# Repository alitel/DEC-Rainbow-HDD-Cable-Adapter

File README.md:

# DEC-Rainbow-HDD-Cable-Adapter
This PCB can be used to connect an MFM hard drive (or emulator) to a Dec rainbow 100 using standard ribbon cables.

I followed the cable building guide found here: https://oldcomputers-ddns.org/public/pub/mirror/os2site/sw/dec/rainbow/rainbow.faq

(The instructions are also found in Cable Instructions.txt)

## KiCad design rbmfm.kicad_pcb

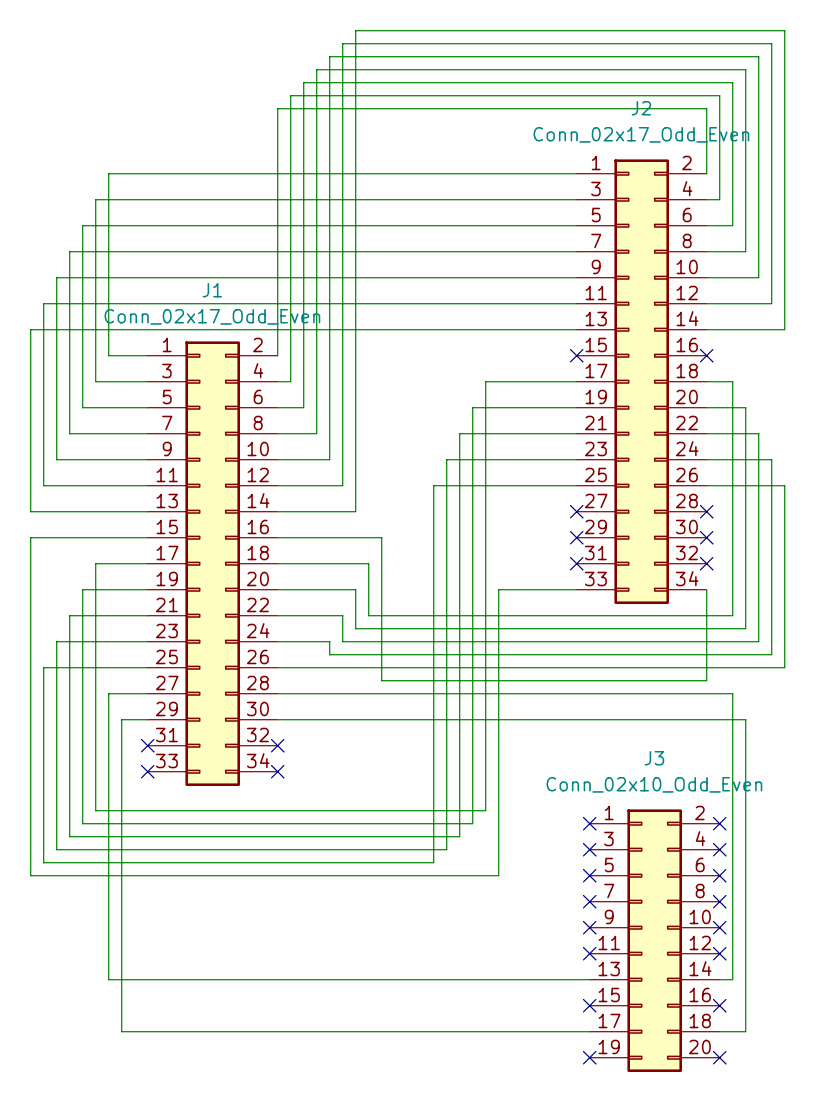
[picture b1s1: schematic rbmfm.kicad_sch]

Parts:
J1, J2: Conn_02x17_Odd_Even; IDC-Header_2x17_P2.54mm_Vertical
J3: Conn_02x10_Odd_Even; IDC-Header_2x10_P2.54mm_Vertical

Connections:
unnamed: J1.1, J2.1
unnamed: J1.2, J2.2
unnamed: J1.3, J2.3
unnamed: J1.4, J2.4
unnamed: J1.5, J2.5
unnamed: J1.6, J2.6
unnamed: J1.7, J2.7
unnamed: J1.8, J2.8
unnamed: J1.9, J2.9
unnamed: J1.10, J2.10
unnamed: J1.11, J2.11
unnamed: J1.12, J2.12
unnamed: J1.13, J2.13
unnamed: J1.14, J2.14
unnamed: J1.15, J2.33
unnamed: J1.16, J2.34
unnamed: J1.17, J2.17
unnamed: J1.18, J2.18
unnamed: J1.19, J2.19
unnamed: J1.20, J2.20
unnamed: J1.21, J2.21
unnamed: J1.22, J2.22
unnamed: J1.23, J2.23
unnamed: J1.24, J2.24
unnamed: J1.25, J2.25
unnamed: J1.26, J2.26
unnamed: J1.27, J3.13
unnamed: J1.28, J3.14
unnamed: J1.29, J3.17
unnamed: J1.30, J3.18

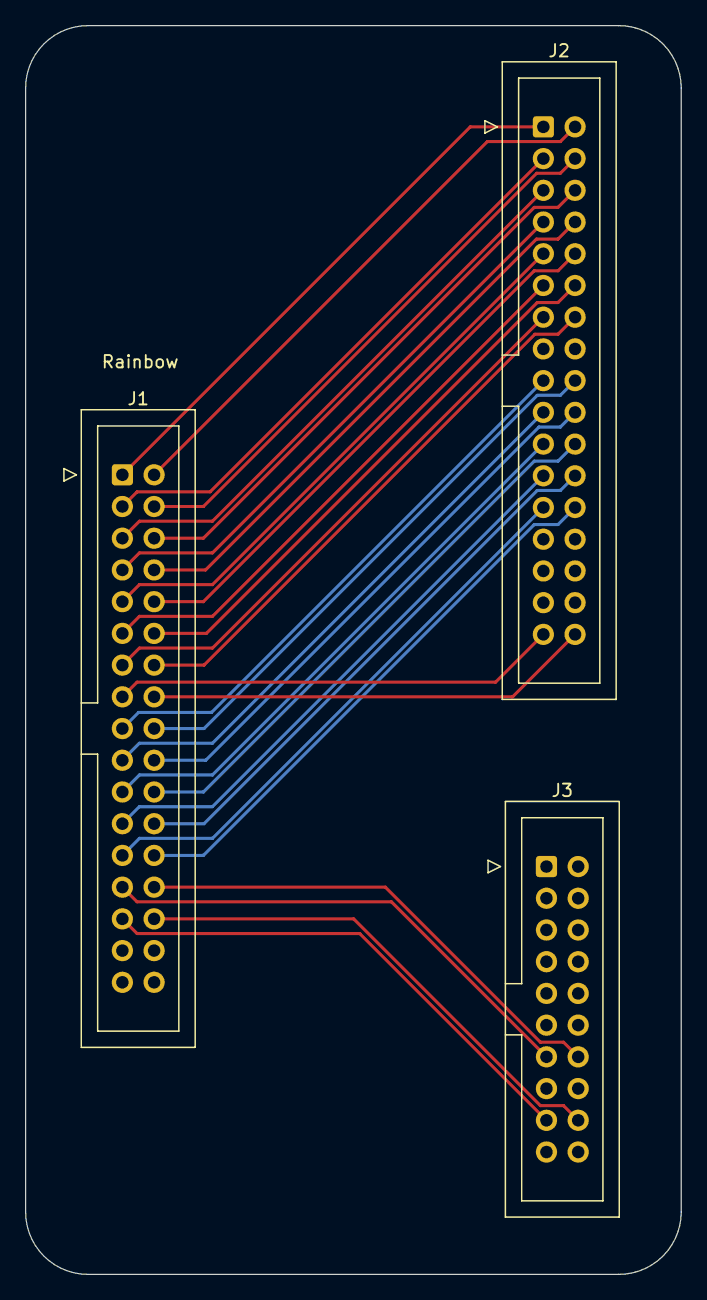
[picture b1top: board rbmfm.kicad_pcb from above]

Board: 2 copper layers, 52.5 x 100.0 mm, 3 parts (0 on the bottom side), 30 nets.

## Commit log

2024-05-13 Add files via upload
    Kicad project files
2024-05-13 Add files via upload
    Added gerber files and zip -- though probably best to regenerate fresh in kicad
